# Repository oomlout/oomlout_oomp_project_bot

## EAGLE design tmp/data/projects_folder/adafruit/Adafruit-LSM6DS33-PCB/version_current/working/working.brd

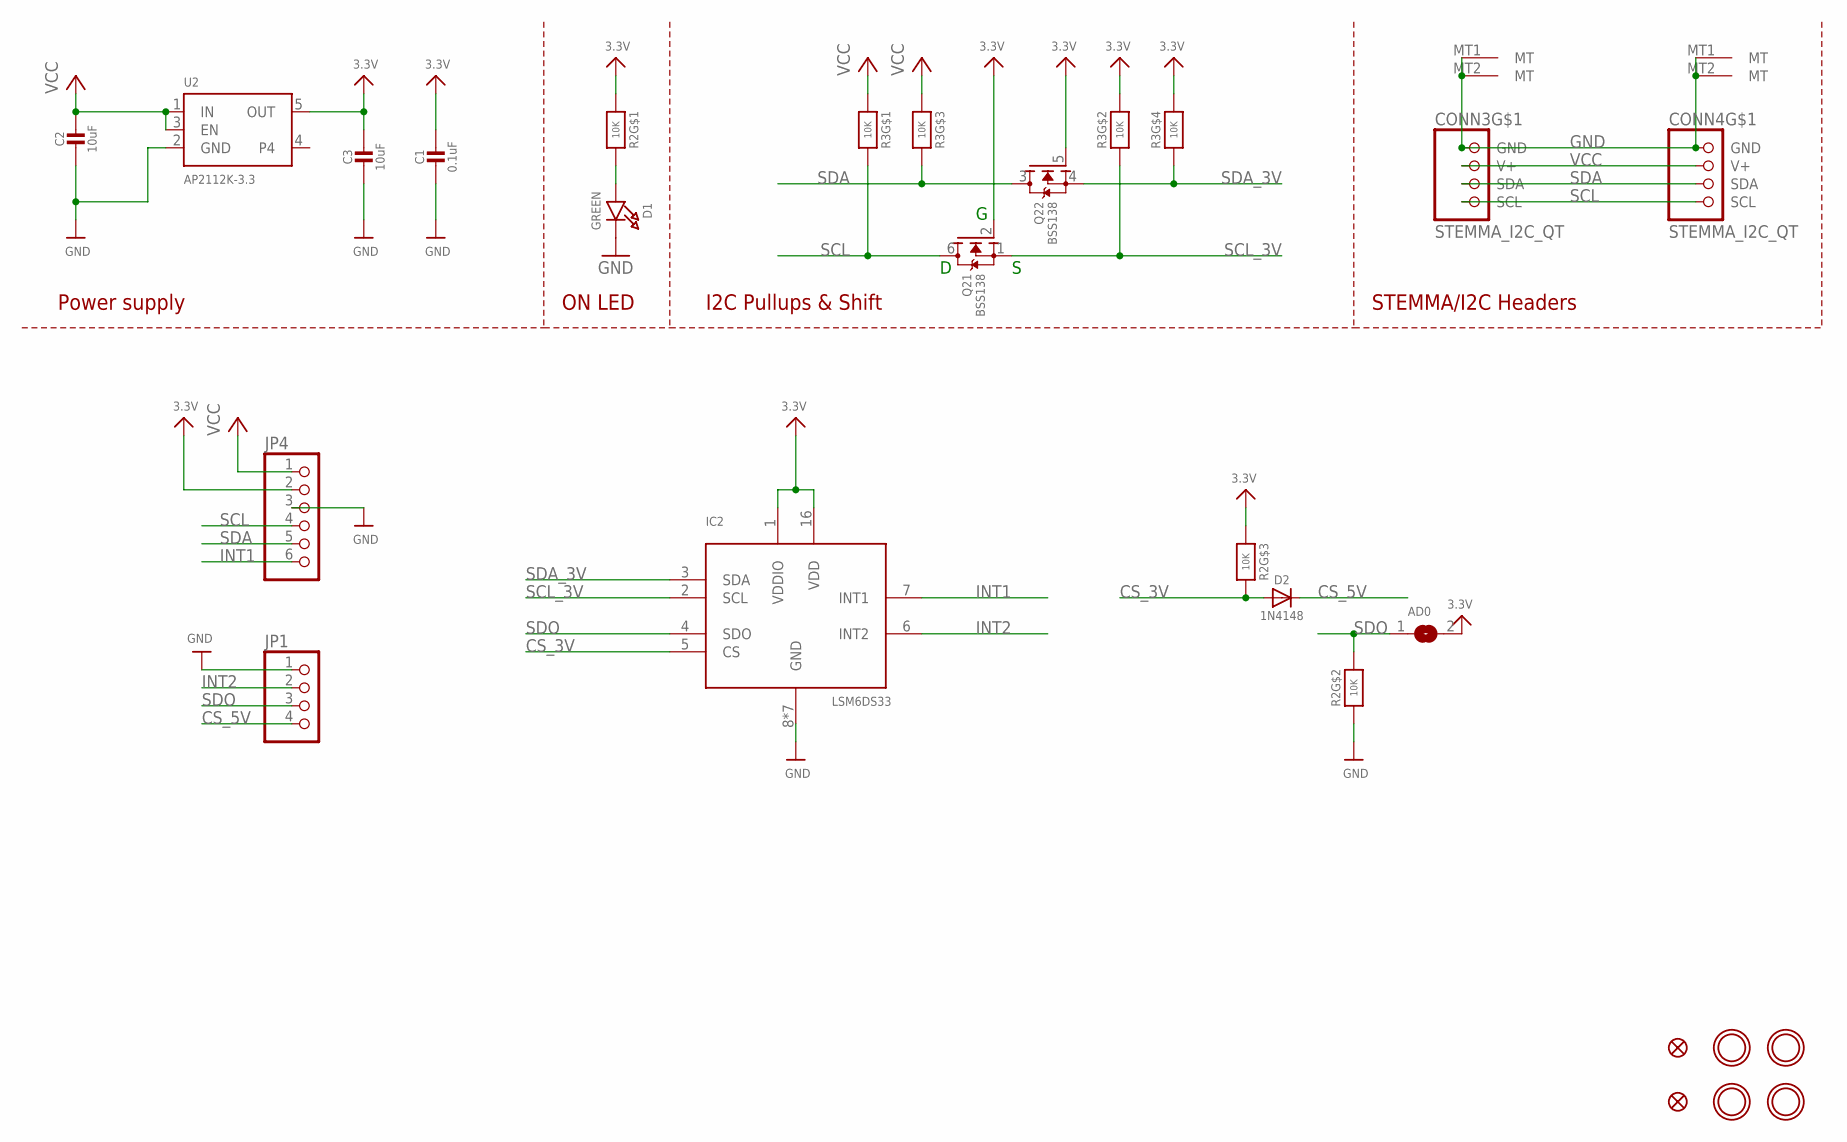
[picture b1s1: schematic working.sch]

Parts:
AD0: SOLDERJUMPER; SOLDERJUMPER_ARROW_NOPASTE
C1: 0.1uF; 0603-NO
C2, C3: 10uF; 0805-NO
CONN3, CONN4: STEMMA_I2C_QT; JST_SH4
D1: GREEN; CHIPLED_0603_NOOUTLINE
D2: 1N4148; SOD-323
FID3, FID4: FIDUCIAL_1MM
IC2: LSM6DS33; LGA16_3X3MM
JP1: HEADER-1X4ROUND; 1X04_ROUND
JP4: HEADER-1X670MIL; 1X06_ROUND_70
Q2: BSS138; SOT363
R2, R3: 10K; RESPACK_4X0603
U2: AP2112K-3.3; SOT23-5
U$1, U$17, U$19, U$21: MOUNTINGHOLE2.5; MOUNTINGHOLE_2.5_PLATED

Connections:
3.3V: AD0.2, C1.1, C3.1, IC2.1 (VDDIO), IC2.16 (VDD), JP4.2, Q2.2 (G), Q2.5 (G), R2.1, R2.3 (1), R3.2 (1), R3.4 (1), U2.5 (OUT)
CS_3V: D2.A, IC2.5 (CS), R2.6 (2)
CS_5V: D2.C, JP1.4
GND: C1.2, C2.2, C3.2, CONN3.1 (GND), CONN3.MT1 (MT), CONN3.MT2 (MT), CONN4.1 (GND), CONN4.MT1 (MT), CONN4.MT2 (MT), D1.C, IC2.8 (GND), IC2.9 (GND), IC2.10 (GND), IC2.11 (GND), IC2.12 (GND), IC2.13 (GND), IC2.15 (GND), JP1.1, JP4.3, R2.2 (1), U2.2 (GND)
INT1: IC2.7 (INT1), JP4.6
INT2: IC2.6 (INT2), JP1.2
unnamed: D1.A, R2.8 (2)
SCL: CONN3.4 (SCL), CONN4.4 (SCL), JP4.4, Q2.6 (D), R3.8 (2)
SCL_3V: IC2.2 (SCL), Q2.1 (S), R3.7 (2)
SDA: CONN3.3 (SDA), CONN4.3 (SDA), JP4.5, Q2.3 (D), R3.6 (2)
SDA_3V: IC2.3 (SDA), Q2.4 (S), R3.5 (2)
SDO: AD0.1, IC2.4 (SDO), JP1.3, R2.7 (2)
VCC: C2.1, CONN3.2 (V+), CONN4.2 (V+), JP4.1, R3.1, R3.3 (1), U2.1 (IN), U2.3 (EN)

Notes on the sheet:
I2C Pullups & Shift
STEMMA/I2C Headers
ON LED
Power supply

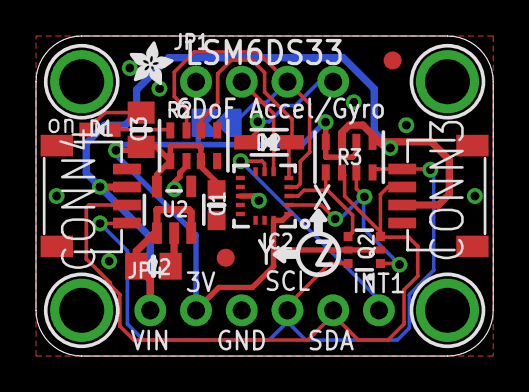
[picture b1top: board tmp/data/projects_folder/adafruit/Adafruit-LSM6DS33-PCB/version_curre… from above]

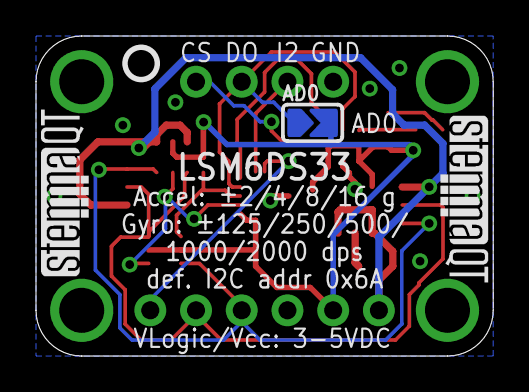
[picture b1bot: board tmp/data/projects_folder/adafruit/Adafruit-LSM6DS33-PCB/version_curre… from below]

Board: 2 copper layers, 25.4 x 17.8 mm, 25 parts (4 on the bottom side), 13 nets.

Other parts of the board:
U$9: ADAFRUIT_2.5MM
U$25: PCBFEAT-REV-040
U$30, U$31: STEMMAQT

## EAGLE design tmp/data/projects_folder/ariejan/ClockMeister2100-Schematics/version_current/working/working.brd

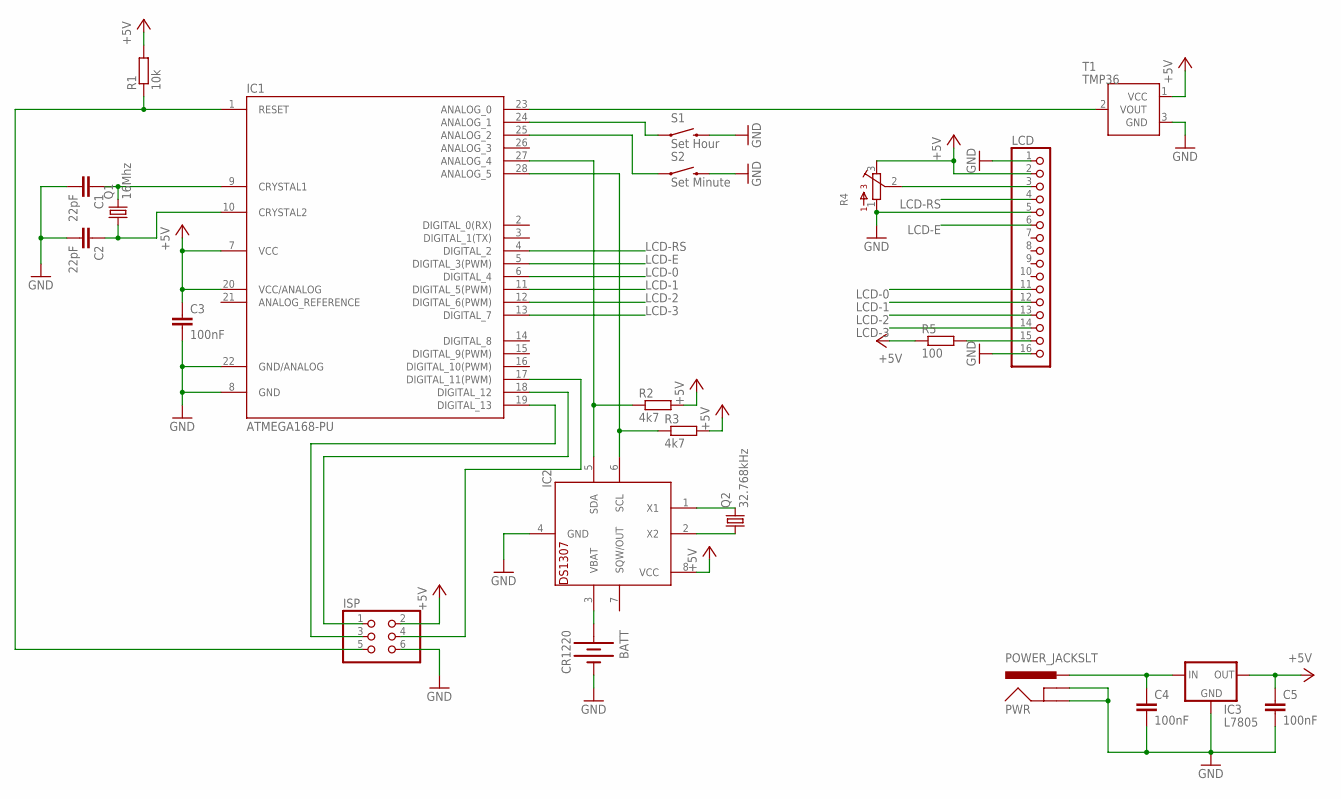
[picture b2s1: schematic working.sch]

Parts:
BATT: CR1220; BATTCON_12MM_PTH; MPN 3001
C1, C2: 22pF; C025-025X050; MPN MCCHU5220J5
C3, C4, C5: 100nF; C025-025X050; MPN MCFYU6104Z6
IC1: ATMEGA168-PU; DIL28-3; MPN ATMEGA328P-PU
IC2: DS1307; DIL08; MPN DS1307+.
IC3: L7805; 78XXS; MPN L7805CV
ISP: PINHD-2X3; 2X03; MPN 826942-3
LCD: PINHD-1X16; 1X16; MPN BBS-116-T-A
PWR: POWER_JACKSLT; POWER_JACK_SLOT
Q1: 16Mhz; HC49/S; MPN HC49SM-3.6864-30-50-60-16-ATF
Q2: 32.768kHz; TC26H; MPN AB38T-32.768KHZ
R1: 10k; 0207/10; MPN MCCFR0W4J0103A50
R2, R3: 4k7; 0207/10; MPN MCF 0.5W 4K7
R4: 3386-F; 3386F
R5: 100; 0207/10; MPN MCCFR0W4J0101A50
S1: Set Hour; TACTILE-PTH; MPN B3F1120
S2: Set Minute; TACTILE-PTH; MPN B3F1120
T1: TMP36; TO92

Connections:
+5V: C3.1, C5.1, IC1.7 (VCC), IC1.20 (VCC/ANALOG), IC2.8 (VCC), IC3.OUT, ISP.2, LCD.2, R1.2, R2.2, R3.2, R4.3, R5.1, T1.1 (VCC)
GND: BATT.GND (-), C1.2, C2.2, C3.2, C4.2, C5.2, IC1.8 (GND), IC1.22 (GND/ANALOG), IC2.4 (GND), IC3.GND, ISP.6, LCD.1, LCD.5, LCD.16, PWR.GND@1 (GNDBREAK), PWR.GND@2 (GND), R4.1, S1.3 (2), S2.3 (2), T1.3 (GND)
LCD-0: IC1.6 (DIGITAL_4), LCD.11
LCD-1: IC1.11 (DIGITAL_5(PWM)), LCD.12
LCD-2: IC1.12 (DIGITAL_6(PWM)), LCD.13
LCD-3: IC1.13 (DIGITAL_7), LCD.14
LCD-E: IC1.5 (DIGITAL_3(PWM)), LCD.6
LCD-RS: IC1.4 (DIGITAL_2), LCD.4
unnamed: LCD.15, R5.2
unnamed: IC1.23 (ANALOG_0), T1.2 (VOUT)
unnamed: IC1.24 (ANALOG_1), S1.1
unnamed: C2.1, IC1.10 (CRYSTAL2), Q1.1
unnamed: C1.1, IC1.9 (CRYSTAL1), Q1.2
unnamed: IC1.25 (ANALOG_2), S2.1
unnamed: C4.1, IC3.IN, PWR.PWR
unnamed: LCD.3, R4.2
unnamed: IC1.28 (ANALOG_5), IC2.6 (SCL), R3.1
unnamed: IC1.27 (ANALOG_4), IC2.5 (SDA), R2.1
unnamed: IC2.1 (X1), Q2.2
unnamed: IC2.2 (X2), Q2.1
unnamed: BATT.VCC@1 (+), IC2.3 (VBAT)
unnamed: IC1.1 (RESET), ISP.5, R1.1
unnamed: IC1.17 (DIGITAL_11(PWM)), ISP.4
unnamed: IC1.18 (DIGITAL_12), ISP.1
unnamed: IC1.19 (DIGITAL_13), ISP.3

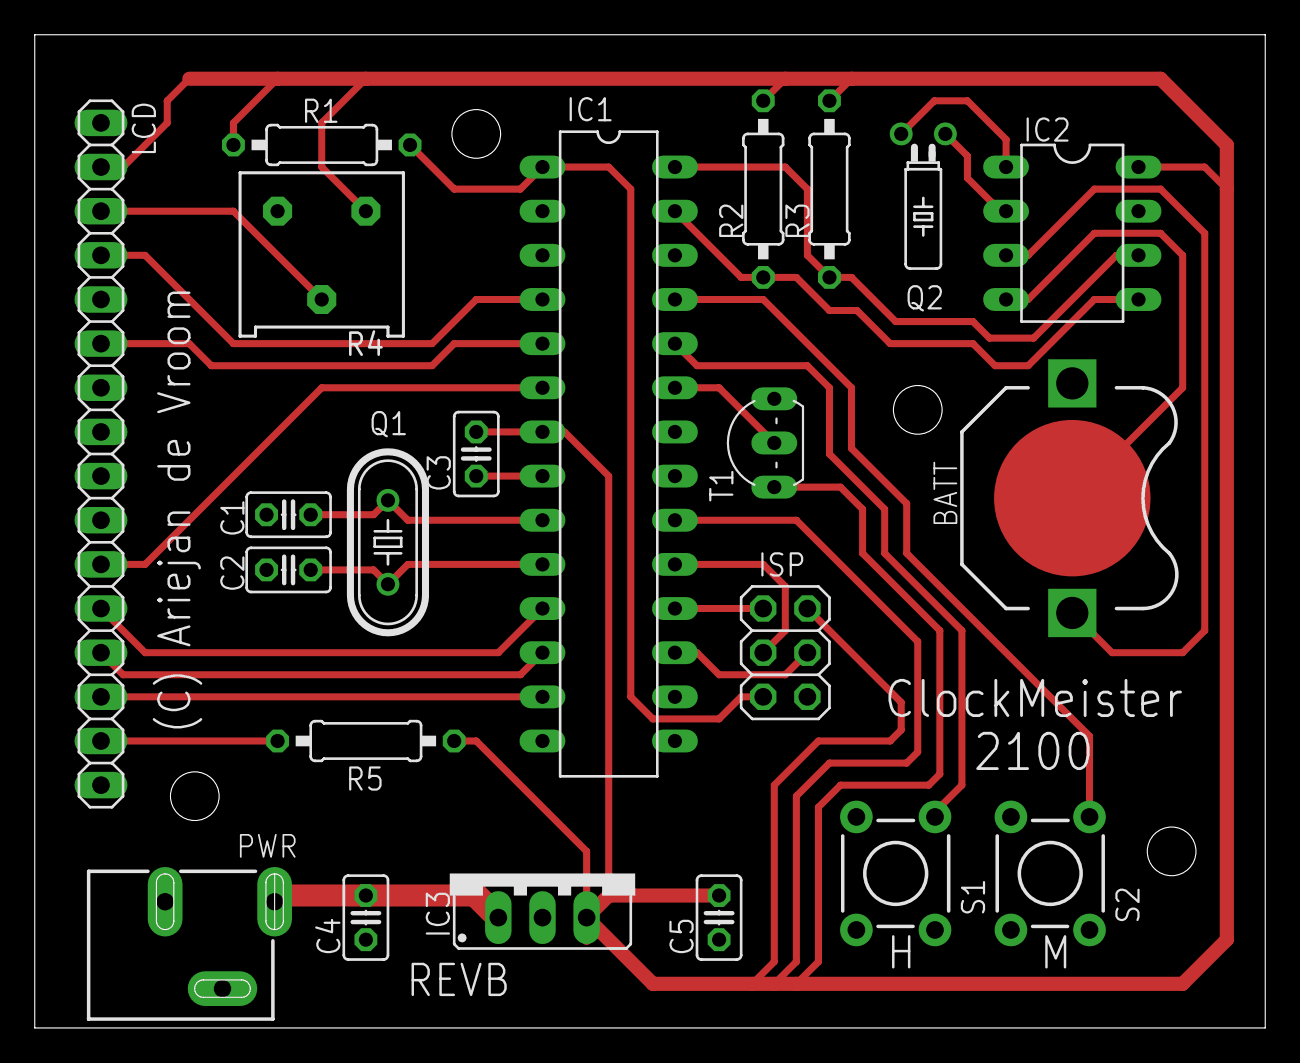
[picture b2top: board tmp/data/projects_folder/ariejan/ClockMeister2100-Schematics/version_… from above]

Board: 2 copper layers, 70.8 x 57.1 mm, 22 parts (0 on the bottom side), 25 nets.

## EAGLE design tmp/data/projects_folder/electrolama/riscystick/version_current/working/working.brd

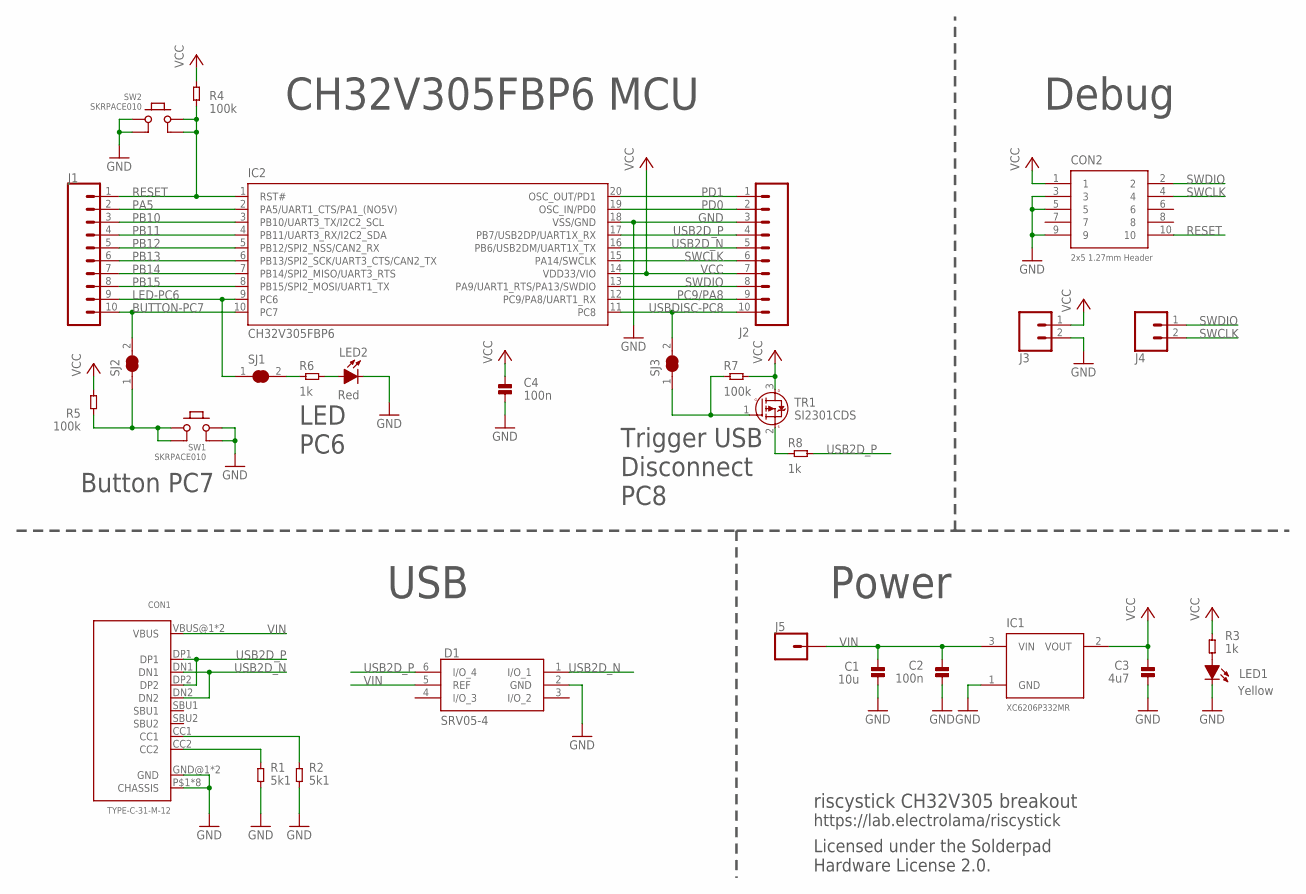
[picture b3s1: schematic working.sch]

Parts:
C1: 10u; _PKG_C_0603; JLCASSY C96446
C2, C4: 100n; _PKG_C_0402; JLCASSY C1525
C3: 4u7; _PKG_C_0402; JLCASSY C23733
CON1: TYPE-C-31-M-12; USBC_C-31-M-12; JLCASSY C165948
CON2: 2x5 1.27mm Header; PZ127VS-12-10-H10-A38; JLCASSY C2935458
D1: SRV05-4; SOT95P280X145-6N; JLCASSY C558453
IC1: XC6206P332MR; SOT96P237X111-3N; JLCASSY C5446
IC2: CH32V305FBP6; TSSOP20-WCH
J1, J2: CONN_10LOCK; 1X10_LOCK
J3, J4: CONN_02LOCK; 1X02_LOCK
J5: CONN_01; 1X01
LED1: Yellow; _PKG_LED_0805; JLCASSY C2296
LED2: Red; _PKG_LED_0805; JLCASSY C84256
R1, R2: 5k1; _PKG_R_0402; JLCASSY C25905
R3, R6, R8: 1k; _PKG_R_0402; JLCASSY C11702
R4, R5, R7: 100k; _PKG_R_0402; JLCASSY C25741
SJ1, SJ2, SJ3: SJ-SHORT
SW1, SW2: SKRPACE010; PUSHBUTTON-4.2X3.2MM; JLCASSY C139797
TR1: SI2301CDS; SOT96P237X111-3N; JLCASSY C10487

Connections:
BUTTON-PC7: IC2.10 (PC7), J1.10, SJ2.2
GND: C1.2, C2.2, C3.2, C4.2, CON1.GND@1 (GND), CON1.GND@2 (GND), CON1.P$1 (CHASSIS), CON1.P$2 (CHASSIS), CON1.P$3 (CHASSIS), CON1.P$4 (CHASSIS), CON1.P$5 (CHASSIS), CON1.P$6 (CHASSIS), CON1.P$7 (CHASSIS), CON1.P$8 (CHASSIS), CON2.3, CON2.5, CON2.9, D1.2 (GND), IC1.1 (GND), IC2.18 (VSS/GND), J2.3, J3.2, LED1.C, LED2.C, R1.1, R2.1, SW1.3 (2_1), SW1.4 (2_2), SW2.1 (1_1), SW2.2 (1_2)
LED-PC6: IC2.9 (PC6), J1.9, SJ1.1
unnamed: R5.2, SJ2.1, SW1.1 (1_1), SW1.2 (1_2)
unnamed: CON1.CC1, R2.2
unnamed: CON1.CC2, R1.2
unnamed: R8.2, TR1.2 (S)
unnamed: LED1.A, R3.1
unnamed: LED2.A, R6.1
unnamed: R6.2, SJ1.2
unnamed: R7.2, SJ3.1, TR1.1 (G)
PA5: IC2.2 (PA5/UART1_CTS/PA1_(NO5V)), J1.2
PB10: IC2.3 (PB10/UART3_TX/I2C2_SCL), J1.3
PB11: IC2.4 (PB11/UART3_RX/I2C2_SDA), J1.4
PB12: IC2.5 (PB12/SPI2_NSS/CAN2_RX), J1.5
PB13: IC2.6 (PB13/SPI2_SCK/UART3_CTS/CAN2_TX), J1.6
PB14: IC2.7 (PB14/SPI2_MISO/UART3_RTS), J1.7
PB15: IC2.8 (PB15/SPI2_MOSI/UART1_TX), J1.8
PC9/PA8: IC2.12 (PC9/PA8/UART1_RX), J2.9
PD0: IC2.19 (OSC_IN/PD0), J2.2
PD1: IC2.20 (OSC_OUT/PD1), J2.1
RESET: CON2.10, IC2.1 (RST#), J1.1, R4.2, SW2.3 (2_1), SW2.4 (2_2)
SWCLK: CON2.4, IC2.15 (PA14/SWCLK), J2.6, J4.2
SWDIO: CON2.2, IC2.13 (PA9/UART1_RTS/PA13/SWDIO), J2.8, J4.1
USB2D_N: CON1.DN1, CON1.DN2, D1.1 (I/O_1), IC2.16 (PB6/USB2DM/UART1X_TX), J2.5
USB2D_P: CON1.DP1, CON1.DP2, D1.6 (I/O_4), IC2.17 (PB7/USB2DP/UART1X_RX), J2.4, R8.1
USBDISC-PC8: IC2.11 (PC8), J2.10, SJ3.2
VCC: C3.1, C4.1, CON2.1, IC1.2 (VOUT), IC2.14 (VDD33/VIO), J2.7, J3.1, R3.2, R4.1, R5.1, R7.1, TR1.3 (D)
VIN: C1.1, C2.1, CON1.VBUS@1 (VBUS), CON1.VBUS@2 (VBUS), D1.5 (REF), IC1.3 (VIN), J5.1

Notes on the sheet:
Button PC7
LED PC6
Trigger USB Disconnect PC8
Debug
Power
USB
CH32V305FBP6 MCU
riscystick CH32V305 breakout
https://lab.electrolama/riscystick
Licensed under the Solderpad Hardware License 2.0.

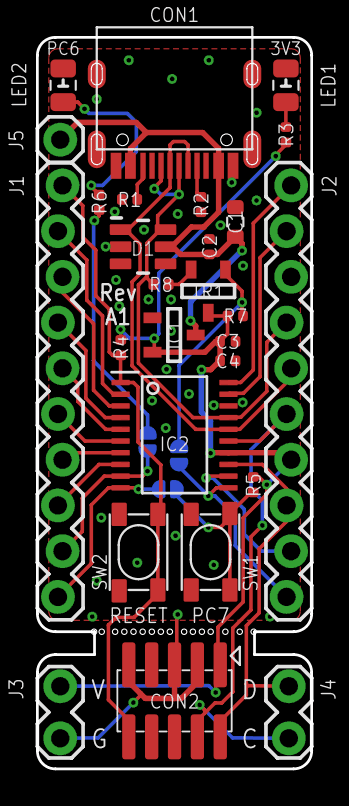
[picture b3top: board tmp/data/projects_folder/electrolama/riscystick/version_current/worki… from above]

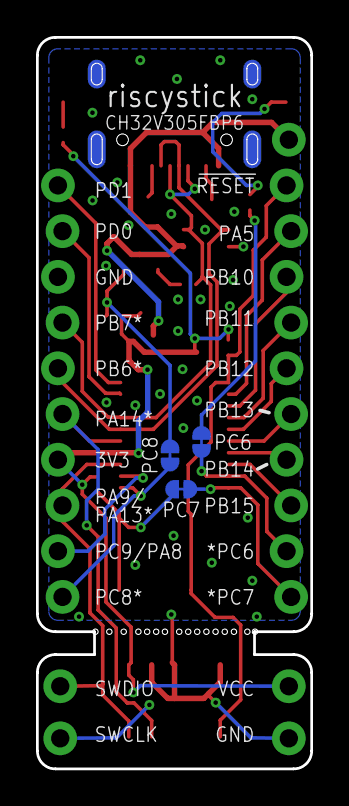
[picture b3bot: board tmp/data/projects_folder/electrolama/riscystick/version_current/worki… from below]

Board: 2 copper layers, 15.2 x 40.6 mm, 30 parts (3 on the bottom side), 29 nets.

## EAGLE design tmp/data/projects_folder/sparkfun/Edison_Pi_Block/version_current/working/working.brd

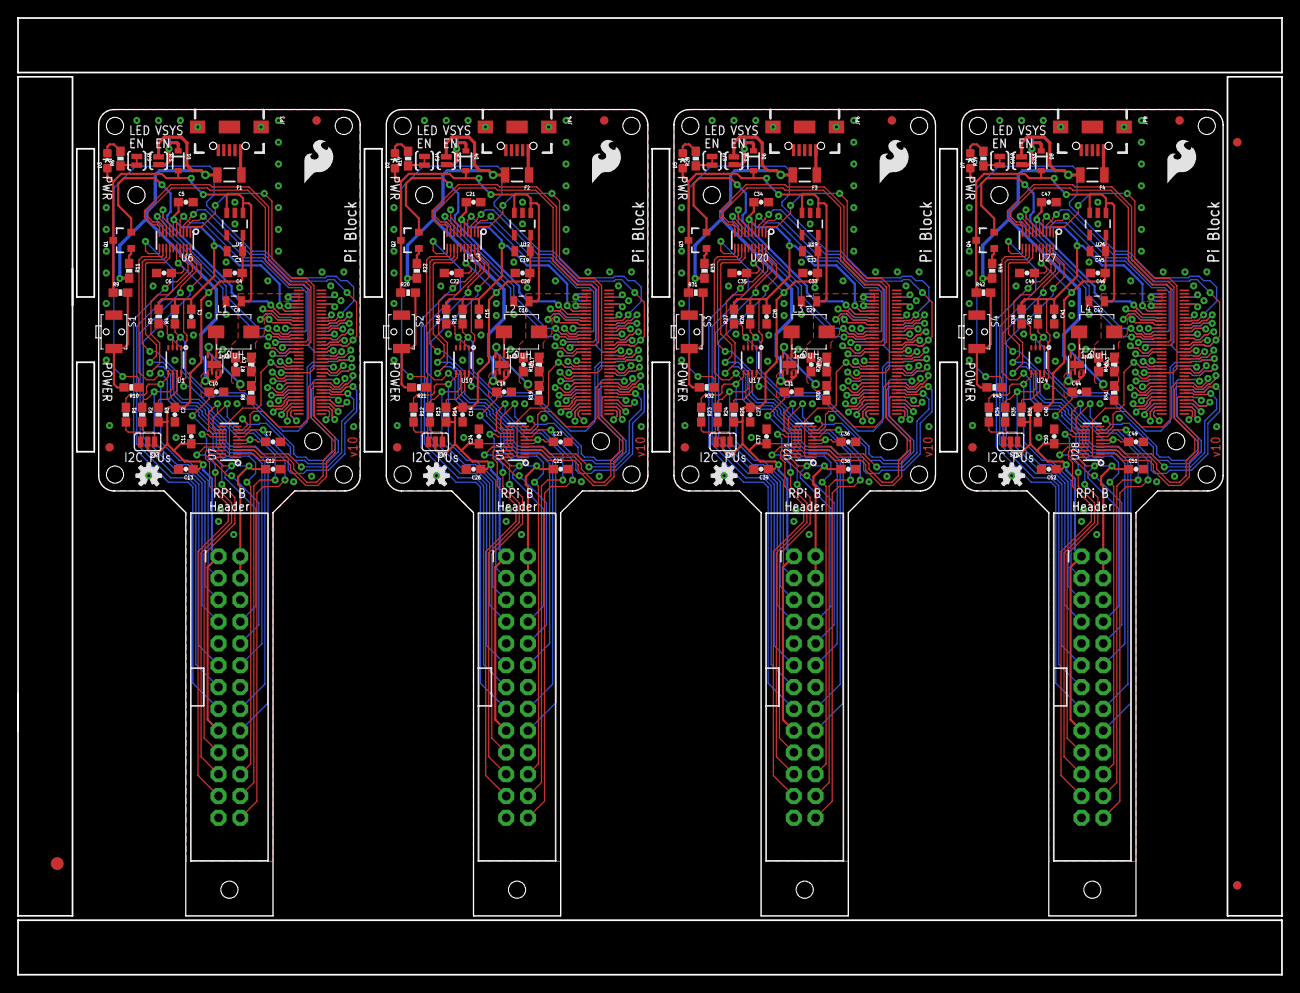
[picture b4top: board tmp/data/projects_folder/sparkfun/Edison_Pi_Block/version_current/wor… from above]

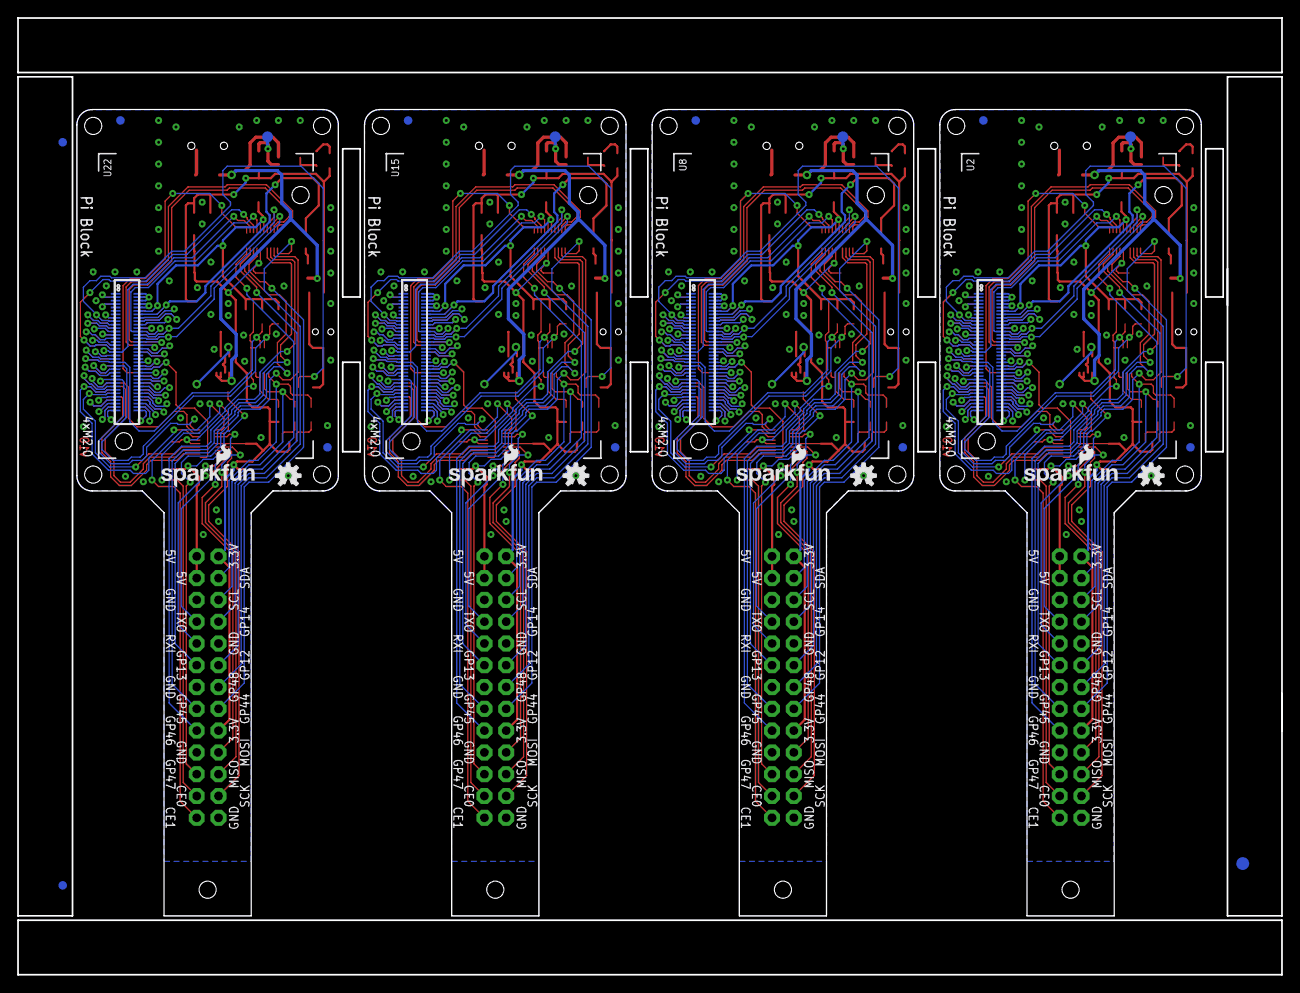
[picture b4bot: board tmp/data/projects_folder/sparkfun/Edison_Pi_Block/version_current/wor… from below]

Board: 2 copper layers, 147.3 x 111.5 mm, 210 parts (31 on the bottom side), 352 nets.

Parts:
C1, C2, C4, C5, C6, C7, C11, C14, C15, C20, C21, C22, C23, C24, C27, C28, C33, C34, C35, C36, C37, C40, C41, C46, C47, C48, C49, C50: 0.1uF; 0603-CAP
C3, C19, C32, C45: 10uF; 0805
C8, C16, C29, C42: 22uF; 0805
C9, C17, C30, C43: 9.0pF; 0603-CAP
C10, C18, C31, C44: 4.7uF; 0603-CAP
C12, C13, C25, C26, C38, C39, C51, C52: 1.0uF; 0603-CAP
D1, D4, D6, D8: BAT20J; SOD-323
D2, D3, D5, D7: BLUE; LED-0603
E$1, E$2: FIDUCIAL-1.5X3
E$3, E$4, E$5, E$6: FIDUCIAL-1X2
F1, F2, F3, F4: PTCSMD; PTC-1206
FID1, FID2, FID3, FID4, FID5, FID6, FID7, FID8, FID9, FID10, FID11, FID12, FID13, FID14, FID15, FID16: FIDUCIAL1X2; FIDUCIAL-1X2
JP1, JP2, JP5, JP7: RASPBERRYPI-GPIOPTH; 2X13-SHROUDED
JP3, JP4, JP6, JP8: USB_MICROB; USB-B-MICRO-SMD_V03
L1, L2, L3, L4: 1.0uH; INDUCTOR-SRP4020
LOGO1, LOGO2, LOGO5, LOGO6, LOGO9, LOGO10, LOGO13, LOGO14: OSHW-LOGOS; OSHW-LOGO-S
LOGO3, LOGO8, LOGO12, LOGO16: SFE_LOGO_FLAME.2_INCH; SFE_LOGO_FLAME_.2
LOGO4, LOGO7, LOGO11, LOGO15: SFE_LOGO_NAME_FLAME.1_INCH; SFE_LOGO_NAME_FLAME_.1
Q1, Q2, Q3, Q4: 200mA/50V; SOT23-3
R1, R2, R9, R12, R13, R20, R23, R24, R31, R34, R35, R42: 10K; 0603-RES
R3, R14, R25, R36: 200k; 0603-RES
R4, R5, R15, R16, R26, R27, R37, R38: DNP; 0603-RES
R6, R11, R17, R22, R28, R33, R39, R44: 1K; 0603-RES
R7, R18, R29, R40: 680k; 0603-RES
R8, R19, R30, R41: 120k; 0603-RES
R10, R21, R32, R43: 220; 0603-RES
S1, S2, S3, S4: POWER; TACTILE_SWITCH-SMD-RIGHT-ANGLE
SJ1, SJ5, SJ8, SJ11: JUMPER-PAD-2-NOYES_SILK; PAD-JUMPER-2-NO_YES_SILK
SJ2, SJ6, SJ9, SJ12: JUMPER-PAD-3-NC_BY_PASTE; PAD-JUMPER-3-NC_BY_PASTE_YES_SILK_FULL_BOX
SJ3, SJ4, SJ7, SJ10: JUMPER-PAD-2-NC_BY_TRACE; PAD-JUMPER-2-NC_BY_TRACE_YES_SILK
TP1, TP2, TP3, TP4: TEST-POINT3X5; PAD.03X.05
U1, U10, U17, U24: PCA9306; PCA9306DC-1:1
U2, U8, U15, U22: EDISON_CONNECTOR_FULLMOUNTING_HOLES; EDISON_DAUGHTER
U3, U9, U16, U23: EDISON_CONNECTOR_FULLHEADER; DF40C-70DP-0.4(51)
U4, U11, U18, U25: TPS62065; WSON-8-PAD
U5, U12, U19, U26: MIC5219 3.3V; SOT23-5
U6, U7, U13, U14, U20, U21, U27, U28: TXB0108; UFDFN-20

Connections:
1.8V: C1.1, C5.1, C7.1, R4.2, R5.2, U1.1, U2.12, U3.12, U6.5, U6.6, U7.5, U7.6
1.8V1: C15.1, C21.1, C23.1, R15.2, R16.2, U8.12, U9.12, U10.1, U13.5, U13.6, U14.5, U14.6
1.8V2: C28.1, C34.1, C36.1, R26.2, R27.2, U15.12, U16.12, U17.1, U20.5, U20.6, U21.5, U21.6
1.8V3: C41.1, C47.1, C49.1, R37.2, R38.2, U22.12, U23.12, U24.1, U27.5, U27.6, U28.5, U28.6
3.3V: U2.8, U2.10, U3.8, U3.10
3.3V1: U8.8, U8.10, U9.8, U9.10
3.3V2: U15.8, U15.10, U16.8, U16.10
3.3V3: U22.8, U22.10, U23.8, U23.10
3.3V_LOCAL: C2.1, C3.1, C4.1, C6.1, C11.1, C13.1, JP1.1, JP1.17, R3.2, SJ2.2, U5.5, U6.16, U7.16
3.3V_LOCAL1: C14.1, C19.1, C20.1, C22.1, C24.1, C26.1, JP2.1, JP2.17, R14.2, SJ6.2, U12.5, U13.16, U14.16
3.3V_LOCAL2: C27.1, C32.1, C33.1, C35.1, C37.1, C39.1, JP5.1, JP5.17, R25.2, SJ9.2, U19.5, U20.16, U21.16
3.3V_LOCAL3: C40.1, C45.1, C46.1, C48.1, C50.1, C52.1, JP7.1, JP7.17, R36.2, SJ12.2, U26.5, U27.16, U28.16
5V: C10.1, C12.1, F1.2, JP1.2, JP1.4, R11.2, SJ1.1, U4.5, U4.7, U4.8
5V1: C18.1, C25.1, F2.2, JP2.2, JP2.4, R22.2, SJ5.1, U11.5, U11.7, U11.8
5V2: C31.1, C38.1, F3.2, JP5.2, JP5.4, R33.2, SJ8.1, U18.5, U18.7, U18.8
5V3: C44.1, C51.1, F4.2, JP7.2, JP7.4, R44.2, SJ11.1, U25.5, U25.7, U25.8
DCIN: Q1.2, U2.14, U3.14
DCIN1: Q2.2, U8.14, U9.14
DCIN2: Q3.2, U15.14, U16.14
DCIN3: Q4.2, U22.14, U23.14
FAULT: U2.19, U3.19
FAULT1: U8.19, U9.19
FAULT2: U15.19, U16.19
FAULT3: U22.19, U23.19
FW_RCVR: U2.69, U3.69
FW_RCVR1: U8.69, U9.69
FW_RCVR2: U15.69, U16.69
FW_RCVR3: U22.69, U23.69
GND: C1.2, C2.2, C3.2, C4.2, C5.2, C6.2, C7.2, C8.2, C10.2, C11.2, C12.2, C13.2, JP1.6, JP1.9, JP1.14, JP1.20, JP1.25, JP3.GND1, JP3.SHIELD1, JP3.SHIELD2, JP3.SHIELD3, R8.1, S1.1, SJ3.1, U1.4, U2.1, U2.5, U2.9, U2.11, U2.13, U2.15, U3.1, U3.5, U3.9, U3.11, U3.13, U3.15, U4.1, U4.3, U4.6, U4.PAD, U5.2, U6.15, U7.15
GND1: C14.2, C15.2, C16.2, C18.2, C19.2, C20.2, C21.2, C22.2, C23.2, C24.2, C25.2, C26.2, JP2.6, JP2.9, JP2.14, JP2.20, JP2.25, JP4.GND1, JP4.SHIELD1, JP4.SHIELD2, JP4.SHIELD3, R19.1, S2.1, SJ4.1, U8.1, U8.5, U8.9, U8.11, U8.13, U8.15, U9.1, U9.5, U9.9, U9.11, U9.13, U9.15, U10.4, U11.1, U11.3, U11.6, U11.PAD, U12.2, U13.15, U14.15
GND2: C27.2, C28.2, C29.2, C31.2, C32.2, C33.2, C34.2, C35.2, C36.2, C37.2, C38.2, C39.2, JP5.6, JP5.9, JP5.14, JP5.20, JP5.25, JP6.GND1, JP6.SHIELD1, JP6.SHIELD2, JP6.SHIELD3, R30.1, S3.1, SJ7.1, U15.1, U15.5, U15.9, U15.11, U15.13, U15.15, U16.1, U16.5, U16.9, U16.11, U16.13, U16.15, U17.4, U18.1, U18.3, U18.6, U18.PAD, U19.2, U20.15, U21.15
GND3: C40.2, C41.2, C42.2, C44.2, C45.2, C46.2, C47.2, C48.2, C49.2, C50.2, C51.2, C52.2, JP7.6, JP7.9, JP7.14, JP7.20, JP7.25, JP8.GND1, JP8.SHIELD1, JP8.SHIELD2, JP8.SHIELD3, R41.1, S4.1, SJ10.1, U22.1, U22.5, U22.9, U22.11, U22.13, U22.15, U23.1, U23.5, U23.9, U23.11, U23.13, U23.15, U24.4, U25.1, U25.3, U25.6, U25.PAD, U26.2, U27.15, U28.15
GP1: U8.48, U9.48, U13.1
GP2: U8.42, U9.42
GP3: U8.34, U9.34
GP4: U8.32, U9.32, U13.10
GP5: U8.30, U9.30, U13.9
GP6: U8.28, U9.28, U13.8
GP7: U8.26, U9.26, U13.7
GP8: U8.25, U9.25
GP9: U8.24, U9.24, U13.4
GP10: U15.48, U16.48, U20.1
GP11: U15.42, U16.42
GP12: U15.34, U16.34
GP12_PWM0: U2.35, U3.35, U6.2
GP12_PWM1: U8.35, U9.35, U13.2
GP12_PWM2: U15.35, U16.35, U20.2
GP12_PWM3: U22.35, U23.35, U27.2
GP13: U15.32, U16.32, U20.10
GP13_PWM1: U2.33, U3.33, U6.3
GP13_PWM2: U8.33, U9.33, U13.3
GP13_PWM3: U15.33, U16.33, U20.3
GP13_PWM4: U22.33, U23.33, U27.3
GP14: U2.48, U3.48, U6.1
GP15: U2.42, U3.42
GP16: U15.30, U16.30, U20.9
GP17: U15.28, U16.28, U20.8
GP18: U15.26, U16.26, U20.7
GP19: U15.25, U16.25
GP19_I2C_1_SCL: R4.1, U1.2, U2.41, U3.41
GP19_I2C_1_SCL1: R15.1, U8.41, U9.41, U10.2
GP19_I2C_1_SCL2: R26.1, U15.41, U16.41, U17.2
GP19_I2C_1_SCL3: R37.1, U22.41, U23.41, U24.2
GP20: U15.24, U16.24, U20.4
GP20_I2C_1_SDA: R5.1, U1.3, U2.43, U3.43
GP20_I2C_1_SDA1: R16.1, U8.43, U9.43, U10.3
GP20_I2C_1_SDA2: R27.1, U15.43, U16.43, U17.3
GP20_I2C_1_SDA3: R38.1, U22.43, U23.43, U24.3
GP21: U22.48, U23.48, U27.1
GP22: U22.42, U23.42
GP23: U22.34, U23.34
GP24: U22.32, U23.32, U27.10
GP25: U22.30, U23.30, U27.9
GP26: U22.28, U23.28, U27.8
GP27: U22.26, U23.26, U27.7
GP27_I2C_6_SCL: U2.45, U3.45
GP27_I2C_6_SCL1: U8.45, U9.45
GP27_I2C_6_SCL2: U15.45, U16.45
GP27_I2C_6_SCL3: U22.45, U23.45
GP28: U22.25, U23.25
GP28_I2C_6_SDA: U2.47, U3.47
GP28_I2C_6_SDA1: U8.47, U9.47
GP28_I2C_6_SDA2: U15.47, U16.47
GP28_I2C_6_SDA3: U22.47, U23.47
GP29: U22.24, U23.24, U27.4
GP40_I2S_2_CLK: U2.52, U3.52
GP40_I2S_2_CLK1: U8.52, U9.52
GP40_I2S_2_CLK2: U15.52, U16.52
GP40_I2S_2_CLK3: U22.52, U23.52
GP41_I2S_2_FS: U2.54, U3.54
GP41_I2S_2_FS1: U8.54, U9.54
GP41_I2S_2_FS2: U15.54, U16.54
GP41_I2S_2_FS3: U22.54, U23.54
GP42_I2S_2_RXD: U2.50, U3.50
GP42_I2S_2_RXD1: U8.50, U9.50
GP42_I2S_2_RXD2: U15.50, U16.50
GP42_I2S_2_RXD3: U22.50, U23.50
GP43_I2S_2_TXD: U2.56, U3.56
GP43_I2S_2_TXD1: U8.56, U9.56
GP43_I2S_2_TXD2: U15.56, U16.56
GP43_I2S_2_TXD3: U22.56, U23.56
GP44: U2.24, U3.24, U6.4
GP45: U2.26, U3.26, U6.7
GP46: U2.28, U3.28, U6.8
GP47: U2.30, U3.30, U6.9
GP48: U2.32, U3.32, U6.10
GP49: U2.34, U3.34
GP77_SD_0_CD#: U2.60, U3.60
GP77_SD_0_CD#1: U8.60, U9.60
GP77_SD_0_CD#2: U15.60, U16.60
GP77_SD_0_CD#3: U22.60, U23.60
GP78_SD_0_CLK: U2.58, U3.58
GP78_SD_0_CLK1: U8.58, U9.58
GP78_SD_0_CLK2: U15.58, U16.58
GP78_SD_0_CLK3: U22.58, U23.58
GP79_SD_0_CMD: U2.62, U3.62
GP79_SD_0_CMD1: U8.62, U9.62
GP79_SD_0_CMD2: U15.62, U16.62
GP79_SD_0_CMD3: U22.62, U23.62
GP80_SD_0_DAT0: U2.66, U3.66
GP80_SD_0_DAT1: U8.66, U9.66
GP80_SD_0_DAT2: U15.66, U16.66
GP80_SD_0_DAT3: U22.66, U23.66
GP81_SD_0_DAT1: U2.70, U3.70
GP81_SD_0_DAT2: U8.70, U9.70
GP81_SD_0_DAT3: U15.70, U16.70
GP81_SD_0_DAT4: U22.70, U23.70
GP82_SD_0_DAT1: U8.64, U9.64
GP82_SD_0_DAT2: U2.64, U3.64
GP82_SD_0_DAT3: U15.64, U16.64
GP82_SD_0_DAT4: U22.64, U23.64
GP83_SD_0_DAT1: U8.68, U9.68
GP83_SD_0_DAT2: U15.68, U16.68
GP83_SD_0_DAT3: U2.68, U3.68
GP83_SD_0_DAT4: U22.68, U23.68
GP84_SD_CLK_FB: U2.44, U3.44
GP84_SD_CLK_FB1: U8.44, U9.44
GP84_SD_CLK_FB2: U15.44, U16.44
GP84_SD_CLK_FB3: U22.44, U23.44
GP109_SPI_2_CLK: U2.55, U3.55, U7.3
GP109_SPI_2_CLK1: U8.55, U9.55, U14.3
GP109_SPI_2_CLK2: U15.55, U16.55, U21.3
GP109_SPI_2_CLK3: U22.55, U23.55, U28.3
GP110_SPI_2_FS0: U2.53, U3.53, U7.8
GP110_SPI_2_FS1: U8.53, U9.53, U14.8
GP110_SPI_2_FS2: U15.53, U16.53, U21.8
GP110_SPI_2_FS3: U22.53, U23.53, U28.8
GP111_SPI_2_FS1: U2.51, U3.51, U7.9
GP111_SPI_2_FS2: U8.51, U9.51, U14.9
GP111_SPI_2_FS3: U15.51, U16.51, U21.9
GP111_SPI_2_FS4: U22.51, U23.51, U28.9
GP114_SPI_2_RXD: U2.59, U3.59, U7.4
GP114_SPI_2_RXD1: U8.59, U9.59, U14.4
GP114_SPI_2_RXD2: U15.59, U16.59, U21.4
GP114_SPI_2_RXD3: U22.59, U23.59, U28.4
GP115_SPI_2_TXD: U2.57, U3.57, U7.7
GP115_SPI_2_TXD1: U8.57, U9.57, U14.7
GP115_SPI_2_TXD2: U15.57, U16.57, U21.7
GP115_SPI_2_TXD3: U22.57, U23.57, U28.7
GP128_UART_1_CTS: U2.65, U3.65
GP128_UART_1_CTS1: U8.65, U9.65
GP128_UART_1_CTS2: U15.65, U16.65
GP128_UART_1_CTS3: U22.65, U23.65
GP129_UART_1_RTS: U2.63, U3.63
GP129_UART_1_RTS1: U8.63, U9.63
GP129_UART_1_RTS2: U15.63, U16.63
GP129_UART_1_RTS3: U22.63, U23.63
GP130_UART_1_RX: U2.61, U3.61, U7.2
GP130_UART_1_RX1: U8.61, U9.61, U14.2
GP130_UART_1_RX2: U15.61, U16.61, U21.2
GP130_UART_1_RX3: U22.61, U23.61, U28.2
GP131_UART_1_TX: U2.46, U3.46, U7.1
GP131_UART_1_TX1: U8.46, U9.46, U14.1
GP131_UART_1_TX2: U15.46, U16.46, U21.1
GP131_UART_1_TX3: U22.46, U23.46, U28.1
GP134_UART_2_RX: U2.22, U3.22
GP134_UART_2_RX1: U8.22, U9.22
GP134_UART_2_RX2: U15.22, U16.22
GP134_UART_2_RX3: U22.22, U23.22
GP135_UART_2_TX: U2.27, U3.27
GP135_UART_2_TX1: U8.27, U9.27
GP135_UART_2_TX2: U15.27, U16.27
GP135_UART_2_TX3: U22.27, U23.27
GP165: U2.25, U3.25
GP182_PWM1: U8.37, U9.37
GP182_PWM2: U2.37, U3.37
GP182_PWM3: U15.37, U16.37
GP182_PWM4: U22.37, U23.37
GP183_PWM1: U8.39, U9.39
GP183_PWM2: U15.39, U16.39
GP183_PWM3: U2.39, U3.39
GP183_PWM4: U22.39, U23.39
HV_SCL: JP1.5, R2.1, U1.6
HV_SCL1: JP2.5, R13.1, U10.6
HV_SCL2: JP5.5, R24.1, U17.6
HV_SCL3: JP7.5, R35.1, U24.6
HV_SDA: JP1.3, R1.1, U1.5
HV_SDA1: JP2.3, R12.1, U10.5
HV_SDA2: JP5.3, R23.1, U17.5
HV_SDA3: JP7.3, R34.1, U24.5
MSIC_SLP_CLK: U2.7, U3.7
MSIC_SLP_CLK1: U8.7, U9.7
MSIC_SLP_CLK2: U15.7, U16.7
MSIC_SLP_CLK3: U22.7, U23.7
unnamed: R3.1, U1.7, U1.8
unnamed: F1.1, JP3.VBUS1
unnamed: D1.C, SJ1.2, TP1.P$1
unnamed: R1.2, SJ2.3
unnamed: R2.2, SJ2.1
unnamed: R14.1, U10.7, U10.8
unnamed: F2.1, JP4.VBUS1
unnamed: D2.C, R17.2
unnamed: R17.1, SJ4.2
unnamed: C17.2, R18.1, R19.2, U11.4
unnamed: L2.P$1, U11.2
unnamed: D3.C, R6.2
unnamed: R6.1, SJ3.2
unnamed: R20.2, R21.2, S2.2
unnamed: R9.2, R10.2, S1.2
unnamed: Q1.1, R11.1
unnamed: Q2.1, R22.1
unnamed: C9.2, R7.1, R8.2, U4.4
unnamed: L1.P$1, U4.2
unnamed: D4.C, SJ5.2, TP2.P$1
unnamed: R12.2, SJ6.3
unnamed: R13.2, SJ6.1
unnamed: R25.1, U17.7, U17.8
unnamed: F3.1, JP6.VBUS1
unnamed: D5.C, R28.2
unnamed: R28.1, SJ7.2
unnamed: C30.2, R29.1, R30.2, U18.4
unnamed: L3.P$1, U18.2
unnamed: R31.2, R32.2, S3.2
unnamed: Q3.1, R33.1
unnamed: D6.C, SJ8.2, TP3.P$1
unnamed: R23.2, SJ9.3
unnamed: R24.2, SJ9.1
unnamed: R36.1, U24.7, U24.8
unnamed: F4.1, JP8.VBUS1
unnamed: D7.C, R39.2
unnamed: R39.1, SJ10.2
unnamed: C43.2, R40.1, R41.2, U25.4
unnamed: L4.P$1, U25.2
unnamed: R42.2, R43.2, S4.2
unnamed: Q4.1, R44.1
unnamed: D8.C, SJ11.2, TP4.P$1
unnamed: R34.2, SJ12.3
unnamed: R35.2, SJ12.1
OSC_CLK_OUT: U2.67, U3.67
OSC_CLK_OUT1: U8.67, U9.67
OSC_CLK_OUT2: U15.67, U16.67
OSC_CLK_OUT3: U22.67, U23.67
PI_CE0: JP1.24, U7.13
PI_CE1: JP1.26, U7.12
PI_CE2: JP2.24, U14.13
PI_CE3: JP2.26, U14.12
PI_CE4: JP5.24, U21.13
PI_CE5: JP5.26, U21.12
PI_CE6: JP7.24, U28.13
PI_CE7: JP7.26, U28.12
PI_GP1: JP2.7, U13.20
PI_GP2: JP2.11, U13.19
PI_GP3: JP2.15, U13.17
PI_GP4: JP1.7, U6.20
PI_GP5: JP2.16, U13.14
PI_GP6: JP2.18, U13.13
PI_GP7: JP2.22, U13.12
PI_GP8: JP2.13, U13.11
PI_GP9: JP5.7, U20.20
PI_GP10: JP5.11, U20.19
PI_GP11: JP5.15, U20.17
PI_GP12: JP5.16, U20.14
PI_GP13: JP5.18, U20.13
PI_GP14: JP5.22, U20.12
PI_GP15: JP5.13, U20.11
PI_GP16: JP7.7, U27.20
PI_GP17: JP1.11, U6.19
PI_GP18: JP7.11, U27.19
PI_GP18#: JP1.12, U6.18
PI_GP18#1: JP2.12, U13.18
PI_GP18#2: JP5.12, U20.18
PI_GP18#3: JP7.12, U27.18
PI_GP19: JP7.15, U27.17
PI_GP20: JP7.16, U27.14
PI_GP21: JP7.18, U27.13
PI_GP22: JP1.15, U6.17
PI_GP23: JP1.16, U6.14
PI_GP24: JP1.18, U6.13
PI_GP25: JP1.22, U6.12
PI_GP26: JP7.22, U27.12
PI_GP27: JP1.13, U6.11
PI_GP28: JP7.13, U27.11
PI_MISO: JP1.21, U7.17
PI_MISO1: JP2.21, U14.17
PI_MISO2: JP5.21, U21.17
PI_MISO3: JP7.21, U28.17
PI_MOSI: JP1.19, U7.14
PI_MOSI1: JP2.19, U14.14
PI_MOSI2: JP5.19, U21.14
PI_MOSI3: JP7.19, U28.14
PI_RXI: JP1.10, U7.19
PI_RXI1: JP2.10, U14.19
PI_RXI2: JP5.10, U21.19
PI_RXI3: JP7.10, U28.19
PI_SCLK: JP1.23, U7.18
PI_SCLK1: JP2.23, U14.18
PI_SCLK2: JP5.23, U21.18
PI_SCLK3: JP7.23, U28.18
PI_TXO: JP1.8, U7.20
PI_TXO1: JP2.8, U14.20
PI_TXO2: JP5.8, U21.20
PI_TXO3: JP7.8, U28.20
PSW: U2.21, U3.21
PSW1: U8.21, U9.21
PSW2: U15.21, U16.21
PSW3: U22.21, U23.21
PWRBTN#: R10.1, U2.17, U3.17
PWRBTN#1: R21.1, U8.17, U9.17
PWRBTN#2: R32.1, U15.17, U16.17
PWRBTN#3: R43.1, U22.17, U23.17
RCVR_MODE: U2.31, U3.31
RCVR_MODE1: U8.31, U9.31
RCVR_MODE2: U15.31, U16.31
RCVR_MODE3: U22.31, U23.31
RESET_OUT#: U2.36, U3.36
RESET_OUT#1: U8.36, U9.36
RESET_OUT#2: U15.36, U16.36
RESET_OUT#3: U22.36, U23.36
USB_DN: U2.18, U3.18
USB_DN1: U8.18, U9.18
USB_DN2: U15.18, U16.18
USB_DN3: U22.18, U23.18
USB_DP: U2.16, U3.16
USB_DP1: U8.16, U9.16
USB_DP2: U15.16, U16.16
USB_DP3: U22.16, U23.16
USB_ID: U2.3, U3.3
USB_ID1: U8.3, U9.3
USB_ID2: U15.3, U16.3
USB_ID3: U22.3, U23.3
USB_VBUS: U2.20, U3.20
USB_VBUS1: U8.20, U9.20
USB_VBUS2: U15.20, U16.20
USB_VBUS3: U22.20, U23.20
VSYS: C8.1, C9.1, D1.A, D3.A, L1.P$2, Q1.3, R7.2, R9.1, U2.2, U2.4, U2.6, U3.2, U3.4, U3.6, U5.1, U5.3
VSYS1: C16.1, C17.1, D2.A, D4.A, L2.P$2, Q2.3, R18.2, R20.1, U8.2, U8.4, U8.6, U9.2, U9.4, U9.6, U12.1, U12.3
VSYS2: C29.1, C30.1, D5.A, D6.A, L3.P$2, Q3.3, R29.2, R31.1, U15.2, U15.4, U15.6, U16.2, U16.4, U16.6, U19.1, U19.3
VSYS3: C42.1, C43.1, D7.A, D8.A, L4.P$2, Q4.3, R40.2, R42.1, U22.2, U22.4, U22.6, U23.2, U23.4, U23.6, U26.1, U26.3
V_BAT_BKUP: U2.23, U3.23
V_BAT_BKUP1: U8.23, U9.23
V_BAT_BKUP2: U15.23, U16.23
V_BAT_BKUP3: U22.23, U23.23

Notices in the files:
parts and their libraries:
microbuilder: This work is placed in the public domain, and may be freely used for commercial and non-commercial work with the following conditions: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
SparkFun-Electromechanical: Licensing: Creative Commons ShareAlike 4.0 International - https://creativecommons.org/licenses/by-sa/4.0
